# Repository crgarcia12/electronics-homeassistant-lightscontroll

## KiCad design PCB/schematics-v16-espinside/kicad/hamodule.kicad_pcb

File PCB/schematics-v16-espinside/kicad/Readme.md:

# Home automation led controller custom module

 This circuit controll home lights following these rules:
 1. Safe: Safety is not trade in any decision.
 1. Fail safe: If this device fails, the ligts are still controllable using the mechanical switches.
 1. Follows standard instalation: This device does not require you to wire your house for it.
 1. It can be installed centrally

 Following those rules and using as a reference a multi-switch light controlled with a mechanical latching relay, this is the wiring idea:

A normal circuit sends all push buttons to the latching relay, which controlls the lights.
This circuit (ESPHome) is a side-car to the latching relay acting as an standard push button, but also sensing the output of the latching relay to detect if the lights are on or off.

# Changes in this version

This version was minimized by:
* Using SPST-NO 3A smaller relays
* Using SMD 3W 200k resistors instead of THT
* Removed external buttons connector
* Removed external leds connector
* Using SMD ULN2003A instead of THT
* Optocoupler THT capacitors replaced by Tantalum SMD
* Using bidirectional optocoupler instead of HCPL3700 to reduce Power dissipation (less current needed)
* Embedding an ESP32 into the board, and adding USB-to-Serial circuitery

Security additions:
* Added fuse at the neutral return from the sensors (F2)
* Resistors are before HCPL3700, to make them work with less than 4V to N, instead of 110V to N

Stability:
* Added filter capacitor to ULN2003A
* Added filter capacitors to LD1117AV33

Others:
* Added led indicator when powered-on

Device schematics (under development)

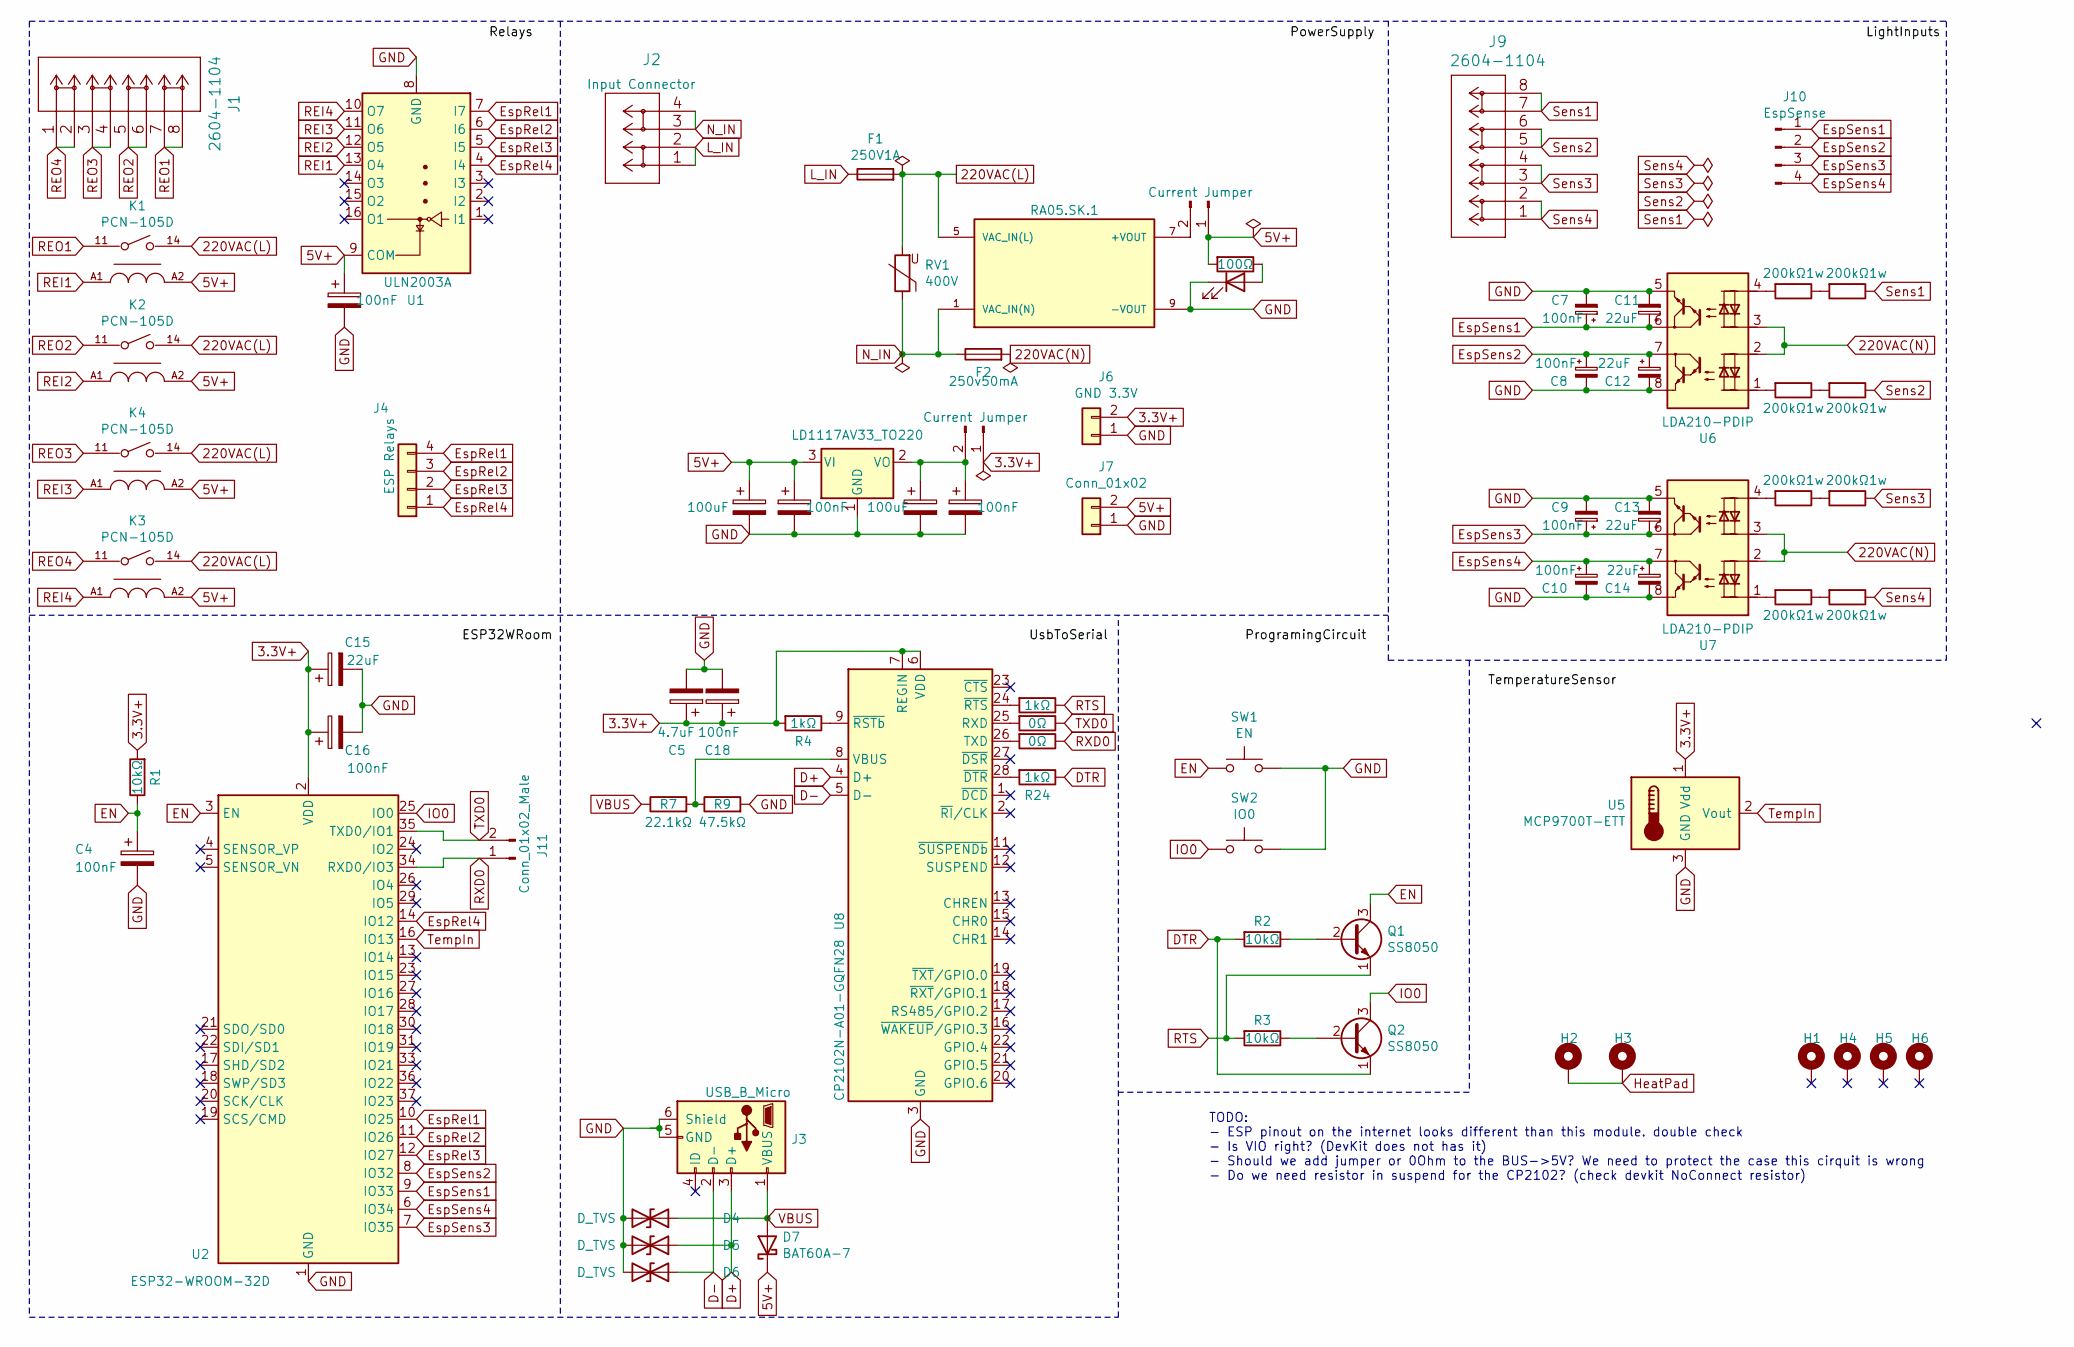
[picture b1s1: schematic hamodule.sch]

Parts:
100uF_1, 100uF_2: 100uF; CP_Radial_D6.3mm_P2.50mm
C1, C2, C3, C4, C7, C8, C9, C10, C16, C18: 100nF; C_0603_1608Metric_Pad1.08x0.95mm_HandSolder; JLCPCB C14663
C5: 4.7uF; C_0603_1608Metric_Pad1.08x0.95mm_HandSolder; JLCPCB C19666
C11, C12, C13, C14: 22uF; CP_EIA-3528-21_Kemet-B_Pad1.50x2.35mm_HandSolder; JLCPCB C110051
C15: 22uF; C_0603_1608Metric_Pad1.08x0.95mm_HandSolder; JLCPCB C59461
D2: LED; LED_0805_2012Metric_Pad1.15x1.40mm_HandSolder; JLCPCB C2297
D4, D5, D6: D_TVS; D_SOD-523; JLCPCB C383211
D7: BAT60A-7; D_SOD-323; JLCPCB C124187
F1: 250V1A; Fuse_Littelfuse_372_D8.50mm
F2: 250v50mA; Fuse_Littelfuse_372_D8.50mm
H1, H4, H5, H6: MountingHole_Pad; MountingHole_3.2mm_M3_ISO14580_Pad
H2, H3: MountingHole_Pad; MountingHole_2.2mm_M2_DIN965_Pad_TopOnly
J1, J9: 2604-1104; big_pads_2604-1104
J2: 2604-1102; big_pads_2604-1102
J3: USB_B_Micro; USB_Micro-B_Molex-105017-0001; JLCPCB C132563
J4: ESP Relays; JST_XH_B4B-XH-A_1x04_P2.50mm_Vertical
J5, J8: Current Jumper; PinHeader_1x02_P2.54mm_Vertical
J6: GND 3.3V; JST_XH_B2B-XH-A_1x02_P2.50mm_Vertical
J7: Conn_01x02; JST_XH_B2B-XH-A_1x02_P2.50mm_Vertical
J10: EspSense; PinSocket_1x04_P2.00mm_Vertical
J11: Conn_01x02_Male; PinHeader_1x02_P2.00mm_Vertical
K1, K2, K3, K4: PCN-105D; bigpads_TE_Connectivity-PCN-124D; coil voltage 24V; current rating 3A; mouser part number 655-PCN-124D3MHZ,000; digikey description RELAY GEN PURPOSE SPST 3A 24V
Q1, Q2: SS8050; SOT-23; JLCPCB C177739
R1, R2, R3: 10kΩ; R_0603_1608Metric_Pad1.05x0.95mm_HandSolder; JLCPCB C25804
R4, R24: 1kΩ; R_0603_1608Metric_Pad1.05x0.95mm_HandSolder; JLCPCB C25585
R5: 1kΩ; R_1206_3216Metric_Pad1.42x1.75mm_HandSolder; JLCPCB C4410
R6, R8: 0Ω; R_0805_2012Metric_Pad1.20x1.40mm_HandSolder; JLCPCB C17477
R7: 22.1kΩ; R_0603_1608Metric_Pad1.05x0.95mm_HandSolder; JLCPCB C25961
R9: 47.5kΩ; R_0603_1608Metric_Pad1.05x0.95mm_HandSolder; JLCPCB C23061
R11: 100Ω; R_0805_2012Metric_Pad1.15x1.40mm_HandSolder; JLCPCB C17408
R16, R17, R18, R19, R20, R21, R22, R23: 200kΩ1w; R_2512_6332Metric_Pad1.52x3.35mm_HandSolder; JLCPCB C38961
RA05.SK.1: RAC05.05SK.277; 277; PARTREV N/A
RV1: 400V; RV_Disc_D12mm_W4.2mm_P7.5mm
SW1: EN; SW_SPST_SKQG_WithStem; JLCPCB C318884
SW2: IO0; SW_SPST_SKQG_WithStem; JLCPCB C318884
U1: ULN2003A; SOIC-16_3.9x9.9mm_P1.27mm; JLCPCB C7512
U2: ESP32-WROOM-32D; ESP32-WROOM-32; JLCPCB C701342
U4: LD1117AV33_TO220; TO-220-3_Vertical
U5: MCP9700T-ETT; SOT-23; JLCPCB C42288
U6, U7: LDA210-PDIP; DIP-8_W7.62mm_Socket_LongPads
U8: CP2102N-A01-GQFN28; QFN-28-1EP_5x5mm_P0.5mm_EP3.35x3.35mm; JLCPCB C105167

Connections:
3.3V+: C5.1, C15.1, C16.1, C18.1, J5.1, J6.2, R1.2, R4.2, U2.2 (VDD), U5.1 (Vdd), U8.6 (VDD), U8.7 (REGIN)
5V+: 100uF_1.1, C1.1, C2.1, D7.1 (K), J7.2, J8.1, K1.A2, K2.A2, K3.A2, K4.A2, R11.2, U1.9 (COM), U4.3 (VI)
220VAC(L): F1.2, K1.14, K2.14, K3.14, K4.14, RA05.SK.1.5 (VAC_IN(L)), RV1.2
220VAC(N): F2.2, U6.2, U6.3, U7.2, U7.3
D+: D5.1 (A1), J3.3 (D+), U8.4 (D+)
D-: D6.1 (A1), J3.2 (D-), U8.5 (D-)
DTR: Q2.1 (E), R2.2, R24.1
EN: C4.1, Q1.3 (C), R1.1, SW1.1, U2.3 (EN)
EspRel1: J4.4, U1.7 (I7), U2.10 (IO25)
EspRel2: J4.3, U1.6 (I6), U2.11 (IO26)
EspRel3: J4.2, U1.5 (I5), U2.12 (IO27)
EspRel4: J4.1, U1.4 (I4), U2.14 (IO12)
EspSens1: C7.1, C11.1, J10.1, U2.9 (IO33), U6.6
EspSens2: C8.1, C12.1, J10.2, U2.8 (IO32), U6.7
EspSens3: C9.1, C13.1, J10.3, U2.7 (IO35), U7.6
EspSens4: C10.1, C14.1, J10.4, U2.6 (IO34), U7.7
GND: 100uF_1.2, 100uF_2.2, C1.2, C2.2, C3.2, C4.2, C5.2, C7.2, C8.2, C9.2, C10.2, C11.2, C12.2, C13.2, C14.2, C15.2, C16.2, C18.2, D2.1 (K), D4.2 (A2), D5.2 (A2), D6.2 (A2), J3.5 (GND), J3.6 (Shield), J6.1, J7.1, R9.2, RA05.SK.1.9 (-VOUT), SW1.2, SW2.2, U1.8 (GND), U2.1 (GND), U2.15 (GND), U2.38 (GND), U2.39 (GND), U4.1 (GND), U5.3 (GND), U6.5, U6.8, U7.5, U7.8, U8.3 (GND), U8.29 (GND)
HeatPad: H2.1, H3.1
IO0: Q2.3 (C), SW2.1, U2.25 (IO0)
L_IN: F1.1, J2.1, J2.2
N_IN: F2.1, J2.3, J2.4, RA05.SK.1.1 (VAC_IN(N)), RV1.1
unnamed: 100uF_2.1, C3.1, J5.2, U4.2 (VO)
unnamed: D2.2 (A), R11.1
unnamed: J8.2, RA05.SK.1.7 (+VOUT)
unnamed: Q1.2 (B), R2.1
unnamed: Q2.2 (B), R3.1
unnamed: R4.1, U8.9 (~RSTb)
unnamed: R5.2, U8.24 (~RTS)
unnamed: R6.2, U8.25 (RXD)
unnamed: R7.2, R9.1, U8.8 (VBUS)
unnamed: R8.2, U8.26 (TXD)
unnamed: R16.1, R20.2
unnamed: R16.2, U6.4
unnamed: R17.1, R21.2
unnamed: R17.2, U6.1
unnamed: R18.1, R22.2
unnamed: R18.2, U7.4
unnamed: R19.1, R23.2
unnamed: R19.2, U7.1
unnamed: R24.2, U8.28 (~DTR)
REI1: K1.A1, U1.13 (O4)
REI2: K2.A1, U1.12 (O5)
REI3: K4.A1, U1.11 (O6)
REI4: K3.A1, U1.10 (O7)
REO1: J1.7, J1.8, K1.11
REO2: J1.5, J1.6, K2.11
REO3: J1.3, J1.4, K4.11
REO4: J1.1, J1.2, K3.11
RTS: Q1.1 (E), R3.2, R5.1
RXD0: J11.1, R8.1, U2.34 (RXD0/IO3)
Sens1: J9.7, J9.8, R20.1
Sens2: J9.5, J9.6, R21.1
Sens3: J9.3, J9.4, R22.1
Sens4: J9.1, J9.2, R23.1
TXD0: J11.2, R6.1, U2.35 (TXD0/IO1)
TempIn: U2.16 (IO13), U5.2 (Vout)
VBUS: D4.1 (A1), D7.2 (A), J3.1 (VBUS), R7.1

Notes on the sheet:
TODO: - ESP pinout on the internet looks different than this module. double check - Is VIO right? (DevKit does not has it) - Should we add jumper or 0Ohm to the BUS->5V? We need to protect the case this cirquit is wrong - Do we need resistor in suspend for the CP2102? (check devkit NoConnect resist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

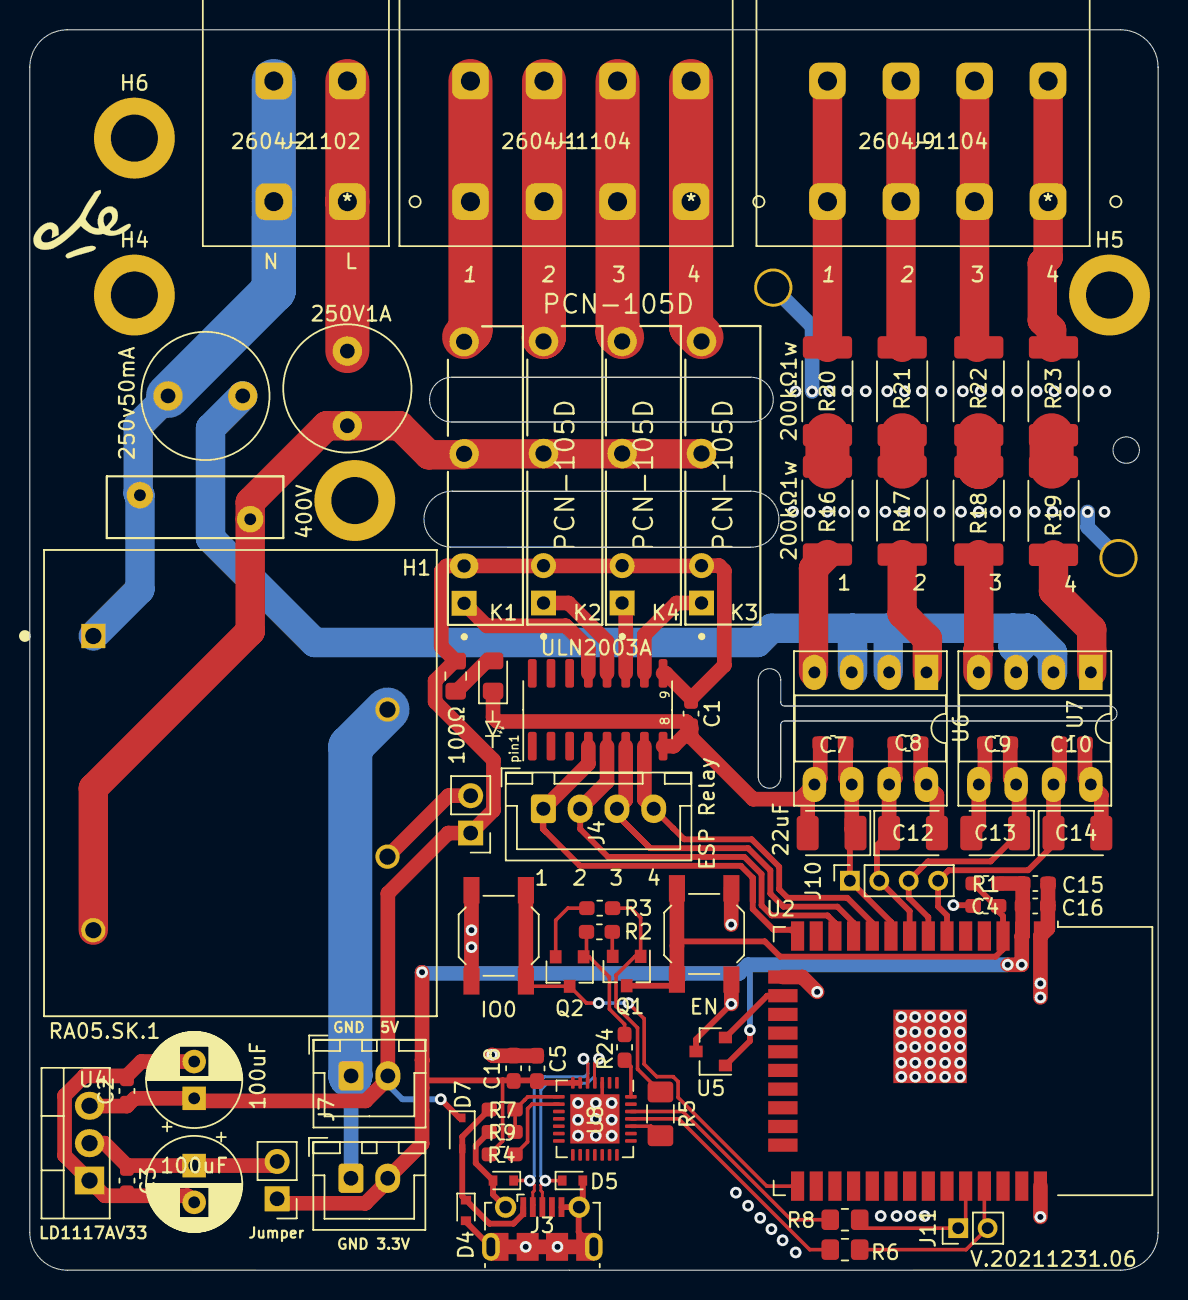
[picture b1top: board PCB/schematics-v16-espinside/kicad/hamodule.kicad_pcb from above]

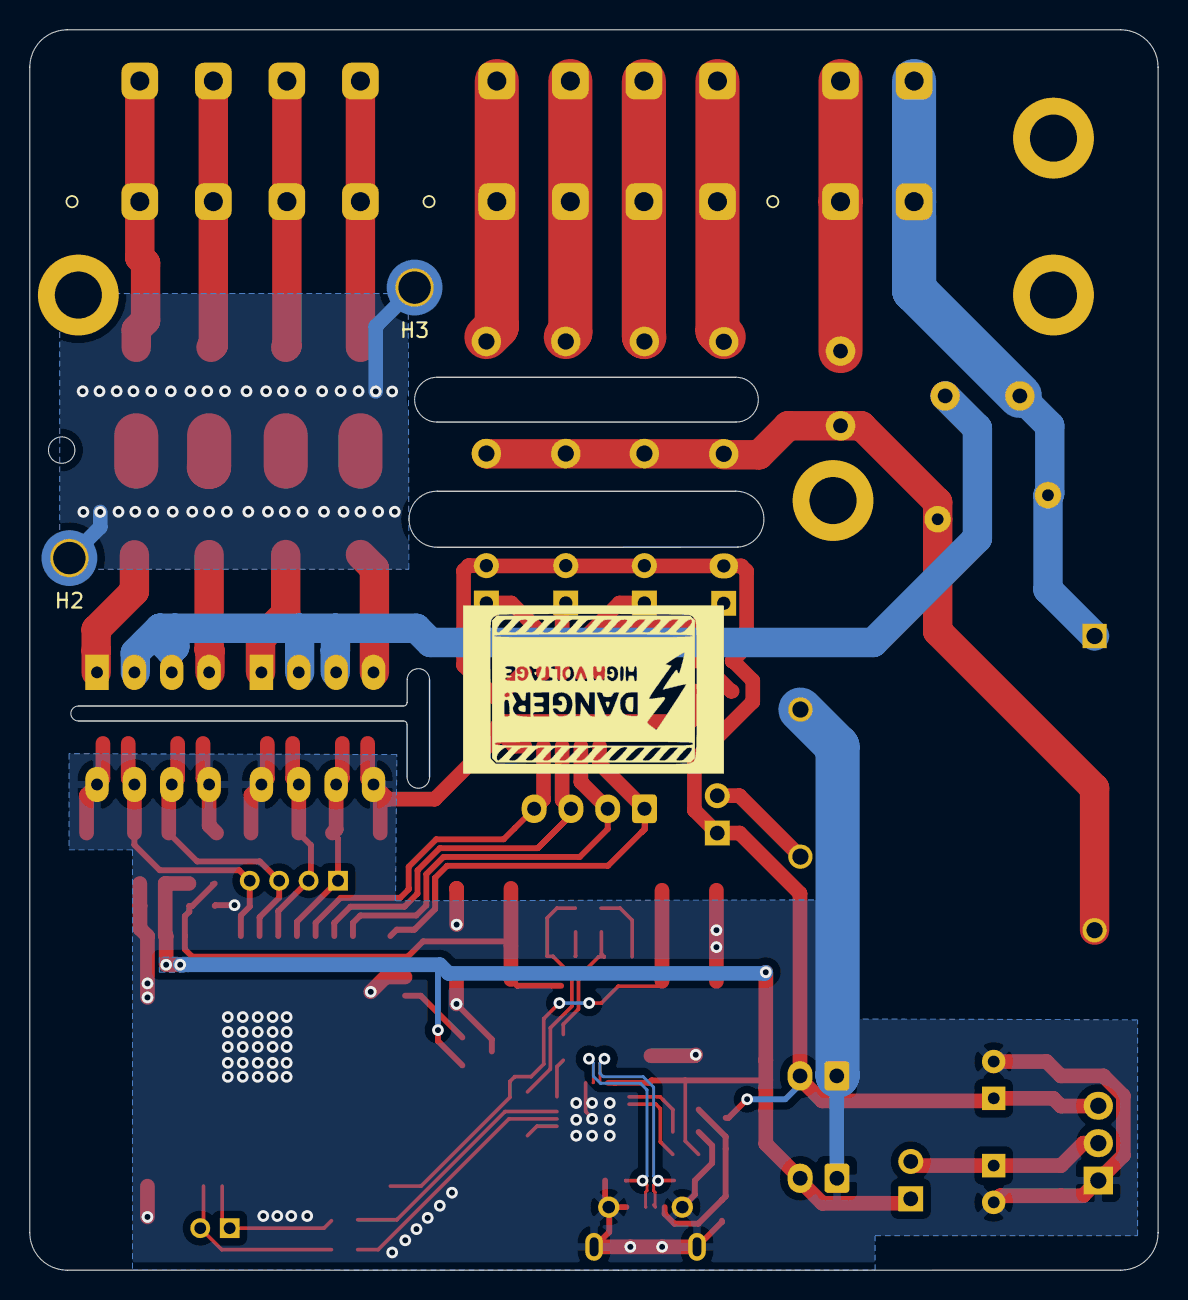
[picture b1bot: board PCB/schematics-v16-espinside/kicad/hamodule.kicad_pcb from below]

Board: 2 copper layers, 76.7 x 84.3 mm, 78 parts (2 on the bottom side), 57 nets.

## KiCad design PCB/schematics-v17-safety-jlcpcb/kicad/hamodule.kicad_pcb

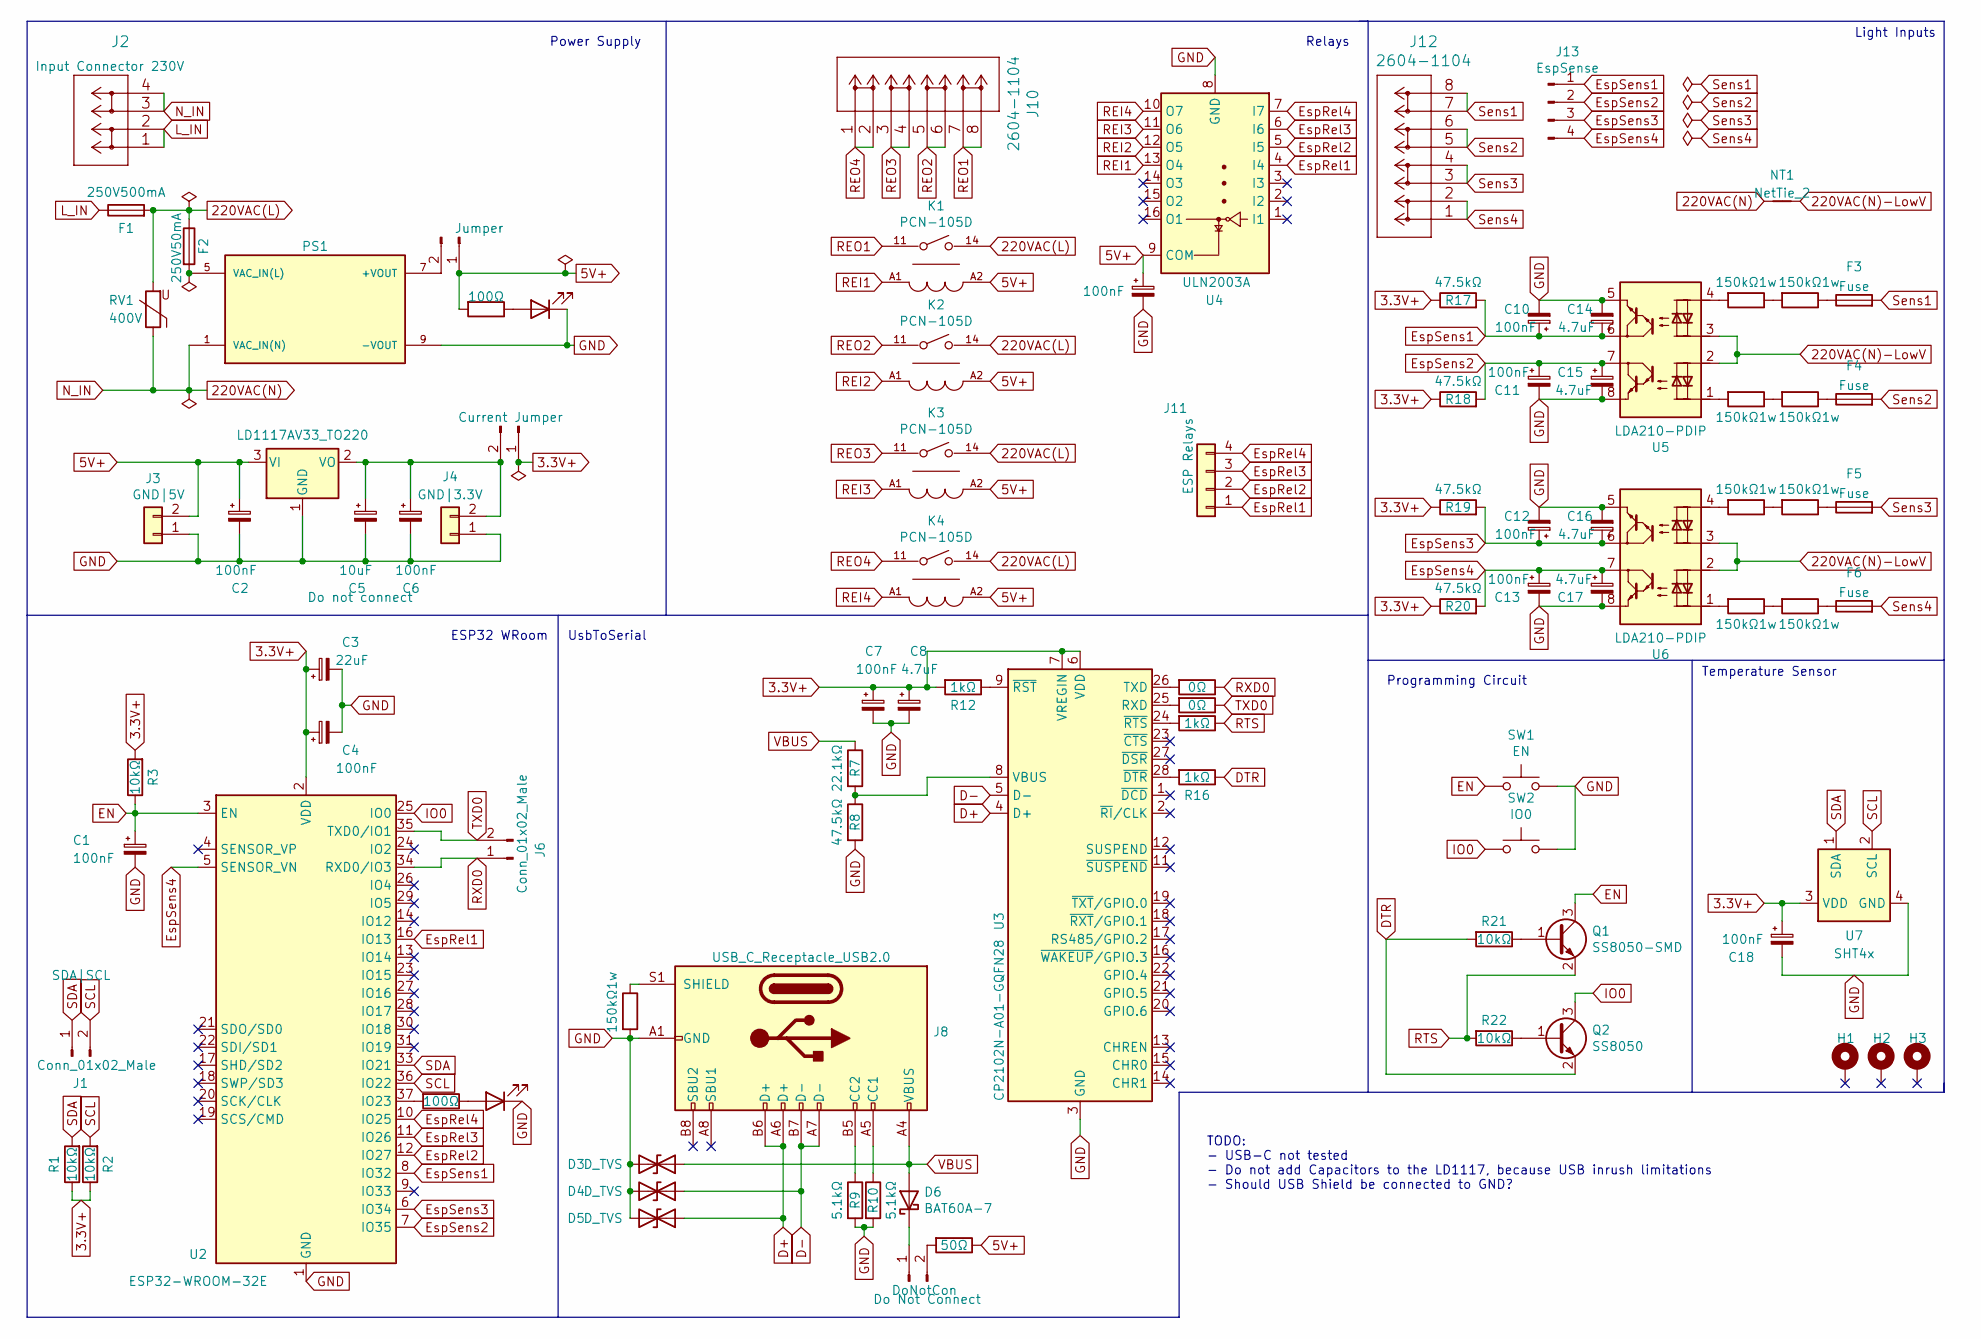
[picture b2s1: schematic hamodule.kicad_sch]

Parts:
C1, C2, C4, C6, C7, C9, C10, C11, C12, C13, C18: 100nF; C_0603_1608Metric_Pad1.08x0.95mm_HandSolder; JLCPCB C14663
C3: 22uF; C_0603_1608Metric_Pad1.08x0.95mm_HandSolder; JLCPCB C59461
C5: 10uF; CP_Radial_D6.3mm_P2.50mm
C8: 4.7uF; C_0603_1608Metric_Pad1.08x0.95mm_HandSolder; JLCPCB C19666
C14, C15, C16, C17: 4.7uF; C_1206_3216Metric_Pad1.33x1.80mm_HandSolder; JLCPCB C29823
D1, D2: LED; LED_0805_2012Metric_Pad1.15x1.40mm_HandSolder; JLCPCB C2297
D3, D4, D5: D_TVS; D_SOD-523; JLCPCB C383211
D6: BAT60A-7; D_SOD-323; JLCPCB C124187
F1: 250V500mA; Fuseholder_TR5_Littelfuse_No560_No460
F2: 250V50mA; Fuseholder_TR5_Littelfuse_No560_No460
F3, F4, F5, F6: Fuse; FUSE_RST-1-BULK
H1, H2, H3: MountingHole_Pad; MountingHole_3.2mm_M3_ISO14580_Pad
J1, J6: Conn_01x02_Male; PinHeader_1x02_P2.54mm_Vertical
J2: 2604-1102; big_pads_2604-1102
J3: GND|5V; JST_XH_B2B-XH-A_1x02_P2.50mm_Vertical
J4: GND|3.3V; JST_XH_B2B-XH-A_1x02_P2.50mm_Vertical
J5: Jumper; PinHeader_1x02_P2.54mm_Vertical
J7: Current Jumper; PinHeader_1x02_P2.54mm_Vertical
J8: USB_C_Receptacle_USB2.0; USB_C_Receptacle_HRO_TYPE-C-31-M-12; JLCPCB C167321
J9: DoNotCon; PinHeader_1x02_P2.54mm_Vertical
J10, J12: 2604-1104; big_pads_2604-1104
J11: ESP Relays; JST_XH_B4B-XH-A_1x04_P2.50mm_Vertical
J13: EspSense; PinSocket_1x04_P2.54mm_Vertical
K1, K2, K3, K4: PCN-105D; bigpads_TE_Connectivity-PCN-124D; coil voltage 24V; current rating 3A; mouser part number 655-PCN-124D3MHZ,000; digikey description RELAY GEN PURPOSE SPST 3A 24V
NT1: NetTie_2; NetTie-2_SMD_Pad2.0mm
PS1: RAC05-05SK/277; 277; PARTREV N/A
Q1: SS8050-SMD; SOT-23; JLCPCB C177739
Q2: SS8050; SOT-23; JLCPCB C177739
R1, R2, R3, R21, R22: 10kΩ; R_0603_1608Metric_Pad0.98x0.95mm_HandSolder; JLCPCB C25804
R4, R5: 100Ω; R_0805_2012Metric_Pad1.20x1.40mm_HandSolder; JLCPCB C17408
R6, R23, R24, R25, R26, R27, R28, R29, R30: 150kΩ1w; R_2512_6332Metric_Pad1.40x3.35mm_HandSolder; JLCPCB C25719
R7: 22.1kΩ; R_0603_1608Metric_Pad0.98x0.95mm_HandSolder; JLCPCB C25961
R8, R17, R18, R19, R20: 47.5kΩ; R_0603_1608Metric_Pad0.98x0.95mm_HandSolder; JLCPCB C23061
R9, R10: 5.1kΩ; R_0603_1608Metric_Pad0.98x0.95mm_HandSolder; JLCPCB C23186
R11: 50Ω; R_0805_2012Metric_Pad1.20x1.40mm_HandSolder; JLCPCB C17738
R12, R16: 1kΩ; R_0603_1608Metric_Pad0.98x0.95mm_HandSolder; JLCPCB C25585
R13, R14: 0Ω; R_0805_2012Metric_Pad1.20x1.40mm_HandSolder; JLCPCB C17477
R15: 1kΩ; R_1206_3216Metric_Pad1.30x1.75mm_HandSolder; JLCPCB C4410
RV1: 400V; RV_Disc_D12mm_W4.2mm_P7.5mm
SW1: EN; SW_SPST_SKQG_WithStem; JLCPCB C318884
SW2: IO0; SW_SPST_SKQG_WithStem; JLCPCB C318884
U1: LD1117AV33_TO220; TO-220-3_Vertical
U2: ESP32-WROOM-32E; ESP32-WROOM-32; JLCPCB C701343
U3: CP2102N-A01-GQFN28; QFN-28-1EP_5x5mm_P0.5mm_EP3.35x3.35mm; JLCPCB C964632
U4: ULN2003A; SOIC-16_3.9x9.9mm_P1.27mm; JLCPCB C7512
U5, U6: LDA210-PDIP; DIP-8_W7.62mm_Socket_LongPads
U7: SHT4x; XDCR_SHT40-AD1B-R2; JLCPCB C2909890

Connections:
3.3V+: C3.1, C4.1, C7.1, C8.1, C18.1, J7.1, R1.1, R2.1, R3.2, R12.2, R17.1, R18.1, R19.1, R20.1, U2.2 (VDD), U3.6 (VDD), U3.7 (VREGIN), U7.3 (VDD)
5V+: C2.1, C9.1, J3.2, J5.1, K1.A2, K2.A2, K3.A2, K4.A2, R5.2, R11.1, U1.3 (VI), U4.9 (COM)
220VAC(L): F1.2, F2.1, K1.14, K2.14, K3.14, K4.14, RV1.2
220VAC(N): J2.3, J2.4, NT1.1, PS1.1 (VAC_IN(N)), RV1.1
220VAC(N)-LowV: NT1.2, U5.2, U5.3, U6.2, U6.3
D+: D5.1 (A1), J8.A6 (D+), J8.B6 (D+), U3.4 (D+)
D-: D4.1 (A1), J8.A7 (D-), J8.B7 (D-), U3.5 (D-)
DTR: Q2.2 (E), R16.1, R21.2
EN: C1.1, Q1.3 (C), R3.1, SW1.1, U2.3 (EN)
EspRel1: J11.1, U2.16 (IO13), U4.4 (I4)
EspRel2: J11.2, U2.12 (IO27), U4.5 (I5)
EspRel3: J11.3, U2.11 (IO26), U4.6 (I6)
EspRel4: J11.4, U2.10 (IO25), U4.7 (I7)
EspSens1: C10.1, C14.1, J13.1, R17.2, U2.8 (IO32), U5.6
EspSens2: C11.1, C15.1, J13.2, R18.2, U2.7 (IO35), U5.7
EspSens3: C12.1, C16.1, J13.3, R19.2, U2.6 (IO34), U6.6
EspSens4: C13.1, C17.1, J13.4, R20.2, U2.5 (SENSOR_VN), U6.7
GND: C1.2, C2.2, C3.2, C4.2, C5.2, C6.2, C7.2, C8.2, C9.2, C10.2, C11.2, C12.2, C13.2, C14.2, C15.2, C16.2, C17.2, C18.2, D1.1 (K), D2.1 (K), D3.2 (A2), D4.2 (A2), D5.2 (A2), J3.1, J4.1, J8.A1 (GND), J8.A12 (GND), J8.B1 (GND), J8.B12 (GND), PS1.9 (-VOUT), R6.2, R8.2, R9.2, R10.2, SW1.2, SW2.2, U1.1 (GND), U2.1 (GND), U2.15 (GND), U2.38 (GND), U2.39 (GND), U3.3 (GND), U3.29 (GND), U4.8 (GND), U5.5, U5.8, U6.5, U6.8, U7.4 (GND)
IO0: Q2.3 (C), SW2.1, U2.25 (IO0)
L_IN: F1.1, J2.1, J2.2
unnamed: C5.1, C6.1, J4.2, J7.2, U1.2 (VO)
unnamed: D1.2 (A), R4.1
unnamed: D2.2 (A), R5.1
unnamed: D6.1 (K), J9.1
unnamed: F2.2, PS1.5 (VAC_IN(L))
unnamed: F3.1, R27.1
unnamed: F4.1, R28.1
unnamed: F5.1, R29.1
unnamed: F6.1, R30.1
unnamed: J5.2, PS1.7 (+VOUT)
unnamed: J8.A5 (CC1), R10.1
unnamed: J8.B5 (CC2), R9.1
unnamed: J8.S1 (SHIELD), R6.1
unnamed: J9.2, R11.2
unnamed: Q1.1 (B), R21.1
unnamed: Q2.1 (B), R22.1
unnamed: R4.2, U2.37 (IO23)
unnamed: R7.2, R8.1, U3.8 (VBUS)
unnamed: R12.1, U3.9 (~RST)
unnamed: R13.2, U3.26 (TXD)
unnamed: R14.2, U3.25 (RXD)
unnamed: R15.2, U3.24 (~RTS)
unnamed: R16.2, U3.28 (~DTR)
unnamed: R23.1, R27.2
unnamed: R23.2, U5.4
unnamed: R24.1, R28.2
unnamed: R24.2, U5.1
unnamed: R25.1, R29.2
unnamed: R25.2, U6.4
unnamed: R26.1, R30.2
unnamed: R26.2, U6.1
REI1: K1.A1, U4.13 (O4)
REI2: K2.A1, U4.12 (O5)
REI3: K3.A1, U4.11 (O6)
REI4: K4.A1, U4.10 (O7)
REO1: J10.7, J10.8, K1.11
REO2: J10.5, J10.6, K2.11
REO3: J10.3, J10.4, K3.11
REO4: J10.1, J10.2, K4.11
RTS: Q1.2 (E), R15.1, R22.2
RXD0: J6.1, R13.1, U2.34 (RXD0/IO3)
SCL: J1.2, R2.2, U2.36 (IO22), U7.2 (SCL)
SDA: J1.1, R1.2, U2.33 (IO21), U7.1 (SDA)
Sens1: F3.2, J12.7, J12.8
Sens2: F4.2, J12.5, J12.6
Sens3: F5.2, J12.3, J12.4
Sens4: F6.2, J12.1, J12.2
TXD0: J6.2, R14.1, U2.35 (TXD0/IO1)
VBUS: D3.1 (A1), D6.2 (A), J8.A4 (VBUS), J8.A9 (VBUS), J8.B4 (VBUS), J8.B9 (VBUS), R7.1

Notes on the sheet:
Programming Circuit
UsbToSerial
Relays
Temperature Sensor
Power Supply
ESP32 WRoom
TODO: - USB-C not tested - Do not add Capacitors to the LD1117, because USB inrush limitations - Should USB Shield be connected to GND?
Light Inputs

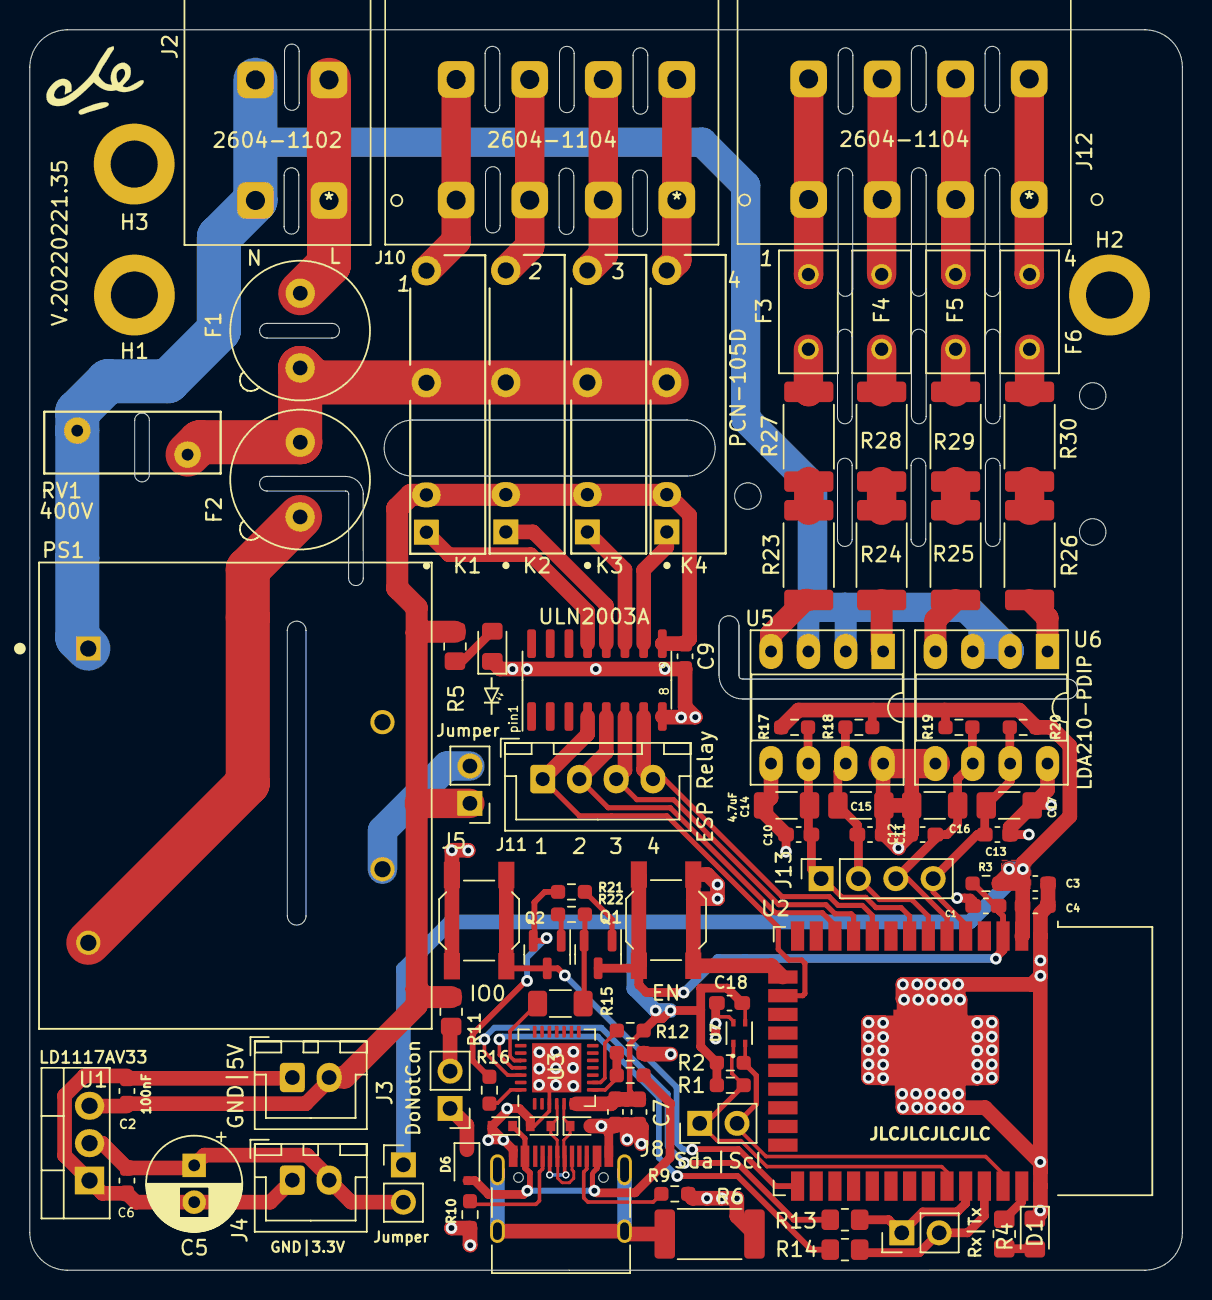
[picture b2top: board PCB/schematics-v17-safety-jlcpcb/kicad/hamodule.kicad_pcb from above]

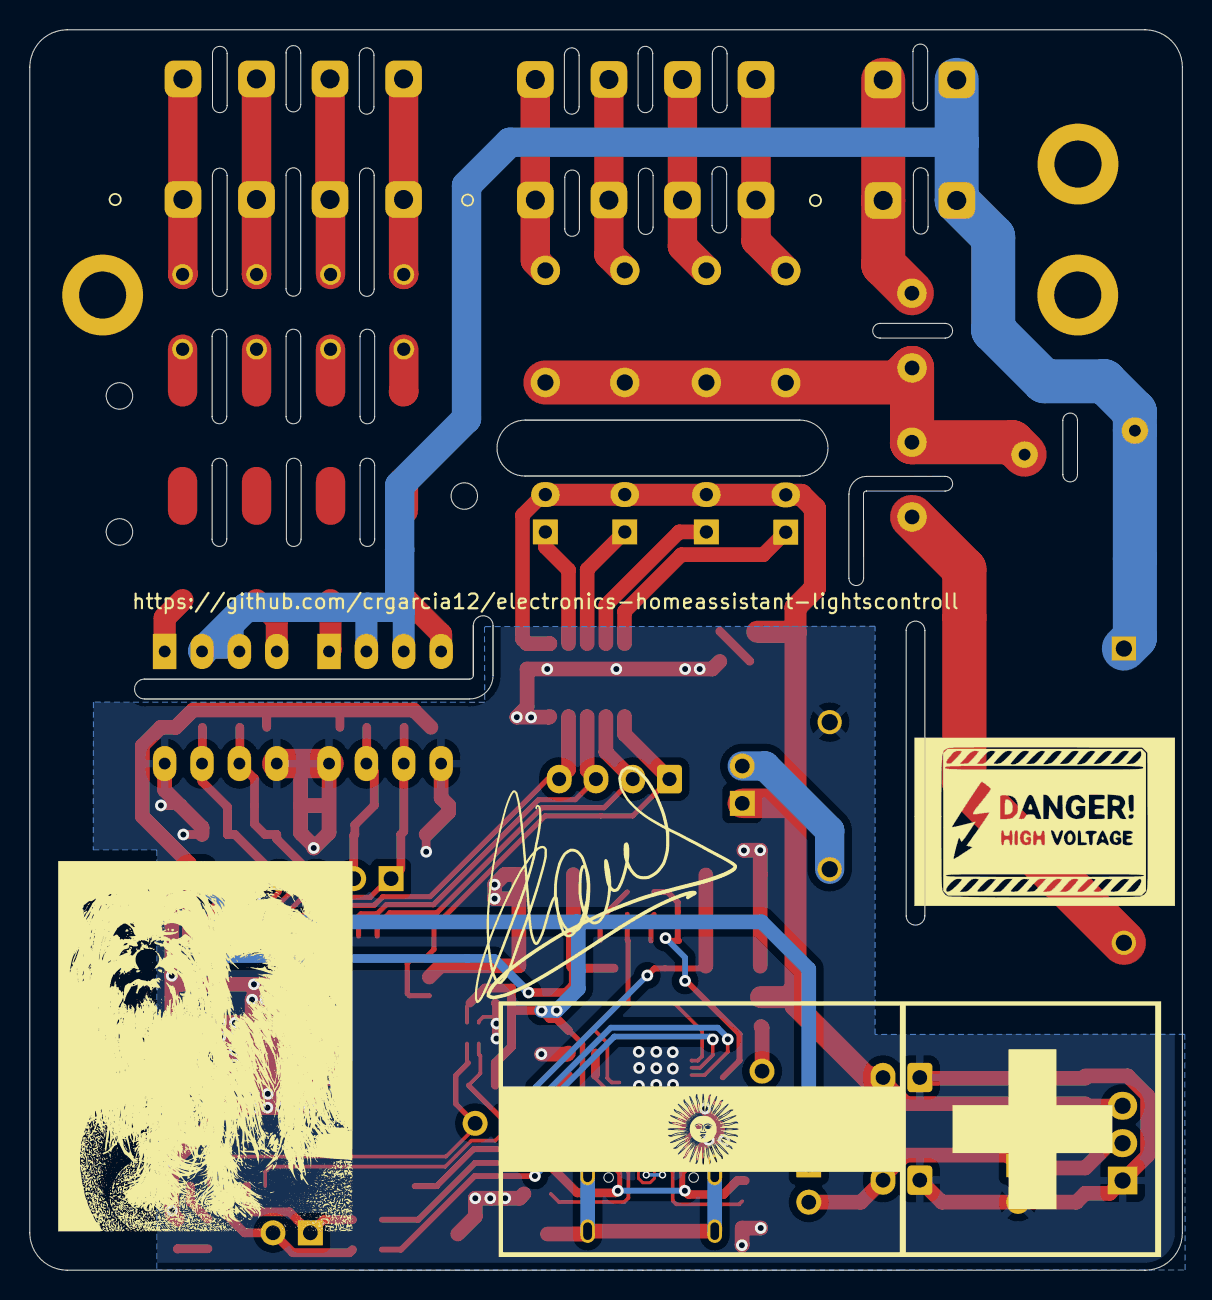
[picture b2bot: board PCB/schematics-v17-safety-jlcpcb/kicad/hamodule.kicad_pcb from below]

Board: 2 copper layers, 78.4 x 84.3 mm, 98 parts (3 on the bottom side), 69 nets.

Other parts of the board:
G1: LOGO; che
G2: LOGO; led_6000dpi
G3: LOGO; danger1_negative
G4: LOGO; depsi

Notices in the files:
parts and their libraries:
Copyright 2021 Accelerated Designs. All rights reserved.
